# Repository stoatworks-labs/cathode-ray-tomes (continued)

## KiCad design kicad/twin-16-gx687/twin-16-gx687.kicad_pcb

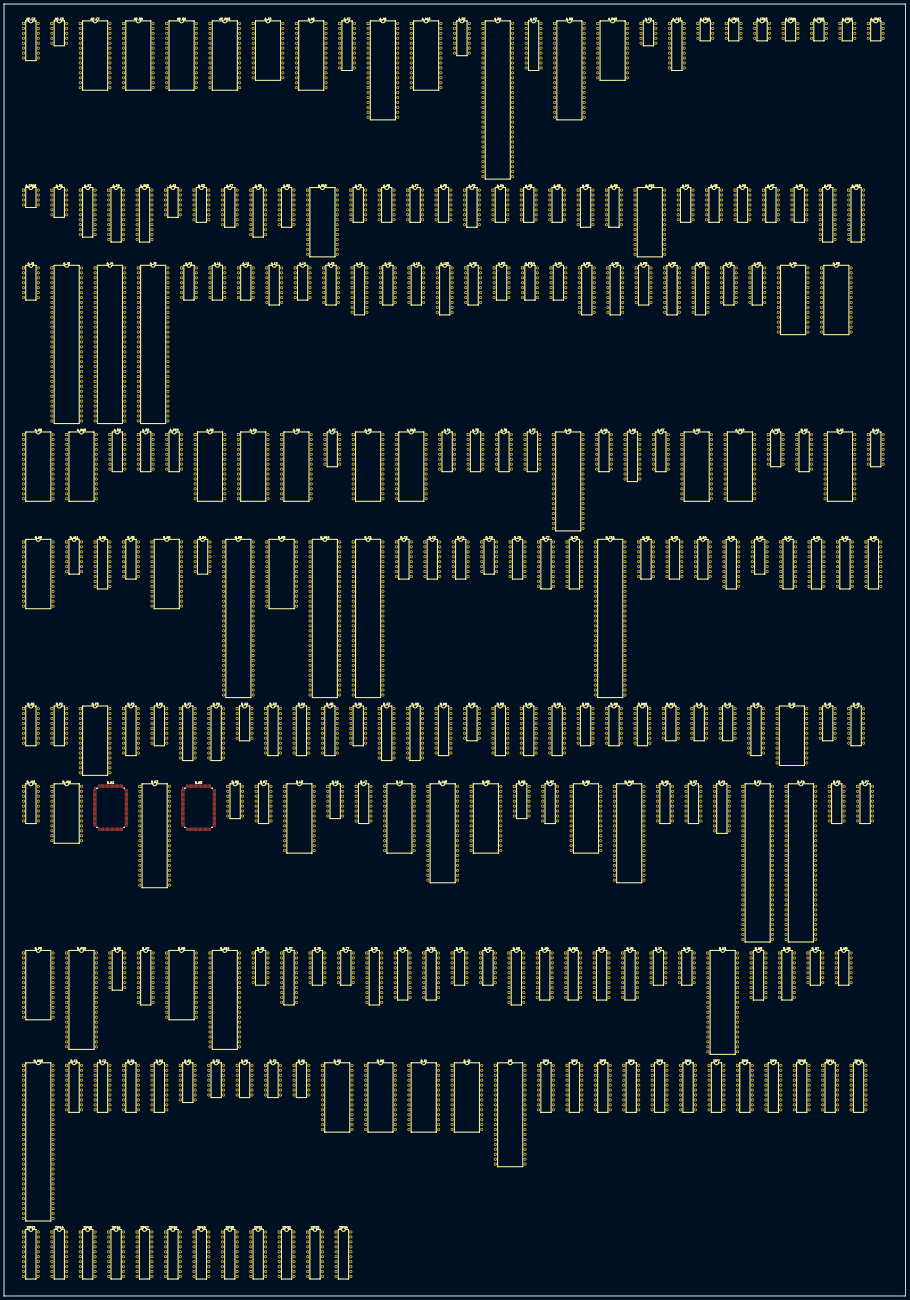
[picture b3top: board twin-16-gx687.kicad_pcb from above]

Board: 2 copper layers, 463.8 x 664.7 mm, 252 parts (0 on the bottom side), 1202 nets, no tracks yet.

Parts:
AP_C2: YM3012; DIP-16_W7.62mm
AP_C5: 007340; DIP-10_W7.62mm
AP_C7: 23C1000; DIP-28_W15.24mm
AP_R4, AP_R6, AP_R10: 27C512; DIP-28_W15.24mm
A_A3: YM2151; DIP-24_W15.24mm
A_A5: 23C1000; DIP-28_W15.24mm
A_A7: 74LS273; DIP-20_W7.62mm
A_A8: Z80CPU; DIP-40_W15.24mm
A_A10: 27C256; DIP-28_W15.24mm
A_B2: uPC324; DIP-14_W7.62mm
A_B4: 007232; DIP-64_W15.24mm
A_B7: 74LS273; DIP-20_W7.62mm
A_B8: μPD7759; DIP-40_W15.24mm
A_B10: 2128SL; DIP-24_W15.24mm
A_C4: 007340; DIP-10_W7.62mm
A_C10: 74LS374; DIP-20_W7.62mm
A_CRA1, A_CRA2, A_CRA3, A_CRA4, A_CRA5, A_CRA6, A_CRA7, A_CRA8: 005273; DIP-8_W7.62mm
A_D1: MB3722; DIP-12_W7.62mm
A_D7: 74LS273; DIP-20_W7.62mm
A_D9, A_D10: 007644; DIP-22_W7.62mm
A_E1: 005924; DIP-12_W7.62mm
A_E3: uPC324; DIP-14_W7.62mm
A_E7: 74LS138; DIP-16_W7.62mm
A_E8: PAL16L8’; DIP-20_W7.62mm
A_E9: 74LS157; DIP-16_W7.62mm
A_E10: 6264SL; DIP-28_W15.24mm
A_F3: uPC324; DIP-14_W7.62mm
A_F6, A_F8: 74LS74; DIP-14_W7.62mm
A_F7: 74LS04; DIP-14_W7.62mm
A_F9: 74LS157; DIP-16_W7.62mm
A_G4: uPC324; DIP-14_W7.62mm
A_G5: 74LS74; DIP-14_W7.62mm
A_G6: 74LS00; DIP-14_W7.62mm
A_G8, A_G9: 74LS157; DIP-16_W7.62mm
A_G10: 6264SL; DIP-28_W15.24mm
A_H4: 74LS08; DIP-14_W7.62mm
A_H5, A_H6: 74LS74; DIP-14_W7.62mm
A_H7: 74LS04; DIP-14_W7.62mm
A_H8: 74LS07; DIP-14_W7.62mm
A_H9, A_H10: 007644; DIP-22_W7.62mm
A_J1: 74LS32; DIP-14_W7.62mm
A_J2: 007791; DIP-64_W15.24mm
A_J4, A_J8: 68000; DIP-64_W15.24mm
A_K1: 74LS32; DIP-14_W7.62mm
A_L1: 74LS07; DIP-14_W7.62mm
A_L2: 74LS00; DIP-14_W7.62mm
A_L3: 74LS138; DIP-16_W7.62mm
A_L4: 74LS74; DIP-14_W7.62mm
A_L5, A_L9: 74LS367; DIP-16_W7.62mm
A_L6, A_L10: 74LS244; DIP-20_W7.62mm
A_L8: 74HC367; DIP-16_W7.62mm
A_M2: 74LS253; DIP-16_W7.62mm
A_M3: 74LS74; DIP-14_W7.62mm
A_M3.4: 74LS02; DIP-14_W7.62mm
A_M4: 74LS21; DIP-14_W7.62mm
A_M5, A_M6, A_M9, A_M10: 74LS245; DIP-20_W7.62mm
A_M8: 74LS138; DIP-16_W7.62mm
A_N2: 74LS253; DIP-16_W7.62mm
A_N3: 74LS139; DIP-16_W7.62mm
A_N4, A_N6, A_N8, A_N10: 27C512; DIP-28_W15.24mm
A_O2: 74LS253; DIP-16_W7.62mm
A_O3: 74LS257; DIP-16_W7.62mm
A_PP2: 74LS253; DIP-16_W7.62mm
A_R8: 27C512; DIP-28_W15.24mm
A_S4, A_S6: 6264SL; DIP-28_W15.24mm
A_S7: 74LS30; DIP-14_W7.62mm
A_S8, A_S10: 27C512; DIP-28_W15.24mm
A_T4: 74LS257; DIP-16_W7.62mm
A_T5, A_T7: 74LS138; DIP-16_W7.62mm
A_T6: 74LS157; DIP-16_W7.62mm
A_U1: 007327; DIP-40_W15.24mm
A_U4: 74LS367; DIP-16_W7.62mm
A_U6: 74LS273; DIP-20_W7.62mm
A_U7: 74LS174; DIP-16_W7.62mm
A_U8, A_U10: 6264SL; DIP-28_W15.24mm
A_V10: 74LS74; DIP-14_W7.62mm
B_A2: 74LS157; DIP-16_W7.62mm
B_A3: 6264SL; DIP-28_W15.24mm
B_A4: 74LS27; DIP-14_W7.62mm
B_A8: SRAM8K8B; DIP-28_W15.24mm
B_A11: 74LS32; DIP-14_W7.62mm
B_B1: 74LS244; DIP-20_W7.62mm
B_B2: 74LS157; DIP-16_W7.62mm
B_B3: 6264SL; DIP-28_W15.24mm
B_B4: 74LS27; DIP-14_W7.62mm
B_B6: 007779; DIP-64_W15.24mm
B_B8: SRAM8K8B; DIP-28_W15.24mm
B_B10: 007780; DIP-64_W15.24mm
B_C1: 007782; DIP-64_W15.24mm
B_C2: 74LS157; DIP-16_W7.62mm
B_C3, B_C4: 74LS174; DIP-16_W7.62mm
B_C5: 74LS32; DIP-14_W7.62mm
B_C6: 74LS138; DIP-16_W7.62mm
B_C7, B_C8: 74LS245; DIP-20_W7.62mm
B_C11: 007781; DIP-64_W15.24mm
B_D2: 74LS157; DIP-16_W7.62mm
B_D3, B_D4: 74LS174; DIP-16_W7.62mm
B_D5, B_D7, B_D8: 74LS245; DIP-20_W7.62mm
B_D6: 74LS02; DIP-14_W7.62mm
B_E2: 74LS273; DIP-20_W7.62mm
B_E5: 74LS245; DIP-20_W7.62mm
B_E6: 74LS153; DIP-16_W7.62mm
B_F2: 74LS157; DIP-16_W7.62mm
B_F3: 27C128; DIP-28_W15.24mm
B_F5: 74LS245; DIP-20_W7.62mm
B_F6: 74LS174; DIP-16_W7.62mm
B_F7, B_F8: 007644; DIP-22_W7.62mm
B_G2: 74LS04; DIP-14_W7.62mm
B_G3, B_G4: 74LS273; DIP-20_W7.62mm
B_G5: 74LS245; DIP-20_W7.62mm
B_G6: 74LS174; DIP-16_W7.62mm
B_G7, B_G8: 007644; DIP-22_W7.62mm
B_H1: 74LS244; DIP-20_W7.62mm
B_H2: 74LS86; DIP-14_W7.62mm
B_H3, B_H4: 74LS273; DIP-20_W7.62mm
B_H5: 74LS245; DIP-20_W7.62mm
B_H8, B_H9, B_H10: 74LS153; DIP-16_W7.62mm
B_H11: 74LS74; DIP-14_W7.62mm
B_J1, B_J2: 74LS86; DIP-14_W7.62mm
B_J5: 74LS245; DIP-20_W7.62mm
B_J6, B_J11: GAL22V10; DIP-24_W15.24mm
B_J8: 74LS32; DIP-14_W7.62mm
B_J9, B_J10: 74LS153; DIP-16_W7.62mm
B_K1: 007783; PQFP-100_14x20mm_P0.65mm
B_K3: 007784; DIP-42_W15.24mm
B_K5: 007785; PQFP-100_14x20mm_P0.65mm
B_K6: 74LS32; DIP-14_W7.62mm
B_K7: 74LS157; DIP-16_W7.62mm
B_L3: 6264SL; DIP-28_W15.24mm
B_L6: 74LS04; DIP-14_W7.62mm
B_L7: 74LS157; DIP-16_W7.62mm
B_L8: SRAM32K8B; DIP-28_W15.24mm
B_L10: 23C4100; DIP-40_W15.24mm
B_M3: 6264SL; DIP-28_W15.24mm
B_M6: 74LS00; DIP-14_W7.62mm
B_M7: 74LS157; DIP-16_W7.62mm
B_M8: SRAM32K8B; DIP-28_W15.24mm
B_M10: 23C4100; DIP-40_W15.24mm
B_N6, B_N7: 74LS157; DIP-16_W7.62mm
B_P1: PAL16L8’; DIP-20_W7.62mm
B_P2, B_P4: 007786; DIP-64_W15.24mm
B_P6, B_P7: 74LS157; DIP-16_W7.62mm
B_P8: SRAM32K8B; DIP-28_W15.24mm
B_P10: 23C4100; DIP-40_W15.24mm
B_R6: 74LS157; DIP-16_W7.62mm
B_R7: 007644; DIP-22_W7.62mm
B_R8: SRAM32K8B; DIP-28_W15.24mm
B_R10: 23C4100; DIP-40_W15.24mm
B_S6: 74LS20; DIP-14_W7.62mm
B_S7: 007644; DIP-22_W7.62mm
B_T6: 74LS32; DIP-14_W7.62mm
B_T7: 74LS02; DIP-14_W7.62mm
B_T8: 007644; DIP-22_W7.62mm
B_T9, B_T10: 74LS374; DIP-20_W7.62mm
B_U6: 74LS32; DIP-14_W7.62mm
B_U7: 74LS02; DIP-14_W7.62mm
B_U8: 007644; DIP-22_W7.62mm
B_U9, B_U10: 74LS374; DIP-20_W7.62mm
B_V5, B_V6: 74LS244; DIP-20_W7.62mm
B_V7, B_V8: 74LS32; DIP-14_W7.62mm
B_W1: 007787; DIP-42_W15.24mm
B_W5, B_W6: 74LS244; DIP-20_W7.62mm
B_W7, B_W8: 74LS32; DIP-14_W7.62mm
B_W10: 007786; DIP-64_W15.24mm
D_C1, D_C2: 74LS245; DIP-20_W7.62mm
D_D1, D_D2: 74LS245; DIP-20_W7.62mm
D_E1: 74LS174; DIP-16_W7.62mm
D_E2: 74LS32; DIP-14_W7.62mm
D_F1: 74LS04; DIP-14_W7.62mm
D_F2: 74LS32; DIP-14_W7.62mm
D_G1: 74LS32; DIP-14_W7.62mm
D_G2: 6264SL; DIP-28_W15.24mm
D_H2: 6264SL; DIP-28_W15.24mm
D_I2: 6264SL; DIP-28_W15.24mm
D_J2: 6264SL; DIP-28_W15.24mm
W3: 007787; DIP-42_W15.24mm
ZIP1, ZIP2, ZIP3, ZIP4, ZIP5, ZIP6, ZIP7, ZIP8, ZIP9, ZIP10, ZIP11, ZIP12, ZIP13, ZIP14, ZIP15, ZIP16, ZIP17, ZIP18, ZIP19, ZIP20, ZIP21, ZIP22, ZIP23, ZIP24: 4464Z; DIP-20_W7.62mm

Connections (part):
+12V: A_D1.10, A_E1.11, A_E3.4, A_F3.4
/1C0: B_C11.50, B_J8.10, B_J10.5
/1C1: B_C11.49, B_J8.9, B_J10.11
/1C2: B_C11.31, B_J8.13, B_J9.5
/1C3: B_C11.30, B_J8.12, B_J9.11
/1C4: B_C11.29, B_H10.5
/1C5: B_C11.2, B_H10.11
/1C6: B_C11.1, B_H8.5, B_J11.11
/1V: B_B6.1, B_C1.50, B_D3.3
/2C0: B_C11.57, B_J10.6, B_J11.4
/2C1: B_C11.56, B_J10.10, B_J11.17
/2C2: B_C11.55, B_J9.6, B_J11.18
/2C3: B_C11.54, B_J9.10, B_J11.19
/2C4: B_C11.53, B_H10.6
/2C5: B_C11.52, B_H10.10
/2C6: B_C11.51, B_H8.6, B_J11.13
/2V: B_C1.51, B_D3.4
/4V: B_C1.52, B_D3.6
/8H: B_C1.46, B_D2.6, B_P1.4
/8V: B_C1.53, B_C2.13
/16H: B_C1.45, B_D2.10
/16V: B_B2.3, B_C1.54
/32H: B_C1.44, B_D2.13
/32V: B_B2.6, B_C1.55
/64H: B_C1.43, B_C2.3
/64V: B_B2.10, B_C1.56
/128H: B_C1.42, B_C2.6
/128V: B_B2.13, B_C1.57
/256H: B_C1.41, B_C2.10
/AB1: AP_R4.10, AP_R6.10, A_E9.14, A_F7.3, A_L6.18, A_M2.14, A_N2.14, A_N4.10, A_N6.10, A_O2.14, A_O3.1, A_PP2.14, A_S4.10, A_S6.10, A_T4.1, A_U1.37, B_B6.25, B_C6.1, B_D2.5, B_K1.16, D_C2.2
/AB2: AP_R4.9, AP_R6.9, A_G9.2, A_L6.16, A_M2.2, A_N2.2, A_N4.9, A_N6.9, A_O2.2, A_PP2.2, A_S4.9, A_S6.9, A_U1.35, B_B6.24, B_C6.2, B_D2.11, B_K1.15, D_C2.3
/AB3: AP_R4.8, AP_R6.8, A_G9.5, A_L6.14, A_N4.8, A_N6.8, A_S4.8, A_S6.8, A_U1.34, B_B6.23, B_C6.3, B_D2.14, B_K1.14, D_C2.4
/AB4: AP_R4.7, AP_R6.7, A_G9.11, A_L6.12, A_N4.7, A_N6.7, A_S4.7, A_S6.7, A_U1.33, B_B6.22, B_C2.2, B_K1.13, D_C2.5
/AB5: AP_R4.6, AP_R6.6, A_G9.14, A_L6.9, A_N4.6, A_N6.6, A_S4.6, A_S6.6, A_U1.32, B_B6.21, B_C2.5, B_K1.12, D_C2.6
/AB6: AP_R4.5, AP_R6.5, A_G8.2, A_L6.7, A_N4.5, A_N6.5, A_S4.5, A_S6.5, A_U1.31, B_B6.20, B_C2.11, B_K1.11, D_C2.7
/AB7: AP_R4.4, AP_R6.4, A_G8.5, A_L6.5, A_N4.4, A_N6.4, A_S4.4, A_S6.4, A_U1.30, B_B6.19, B_C2.14, B_K1.10, D_C2.8
/AB8: AP_R4.3, AP_R6.3, A_G8.11, A_L6.3, A_N4.3, A_N6.3, A_S4.3, A_S6.3, A_U1.29, B_B2.2, B_B6.18, B_K1.9, D_C2.9
/AB9: AP_R4.25, AP_R6.25, A_G8.14, A_L5.3, A_N4.25, A_N6.25, A_S4.25, A_S6.25, A_T6.2, B_B2.5, B_B6.17, B_K1.8, D_D2.2
/AB10: AP_R4.24, AP_R6.24, A_F9.2, A_L5.5, A_N4.24, A_N6.24, A_S4.24, A_S6.24, A_T6.5, B_B2.11, B_B6.15, B_K1.7, D_D2.3
/AB11: AP_R4.21, AP_R6.21, A_F9.5, A_L5.7, A_N4.21, A_N6.21, A_S4.21, A_S6.21, A_T6.11, B_B2.14, B_B6.14, B_K1.6
/AB12: AP_R4.23, AP_R6.23, A_F9.11, A_L5.9, A_N4.23, A_N6.23, A_S4.23, A_S6.23, A_T6.14, B_A2.2, B_B6.13, B_K1.5
/AB13: AP_R4.2, AP_R6.2, A_F9.14, A_L5.11, A_N4.2, A_N6.2, A_S4.2, A_S6.2, B_A2.5, B_E6.12, B_K1.4
/Battery Powered RAM/AB'1: D_C2.18, D_G2.10, D_H2.10, D_I2.10, D_J2.10
/Battery Powered RAM/AB'2: D_C2.17, D_G2.9, D_H2.9, D_I2.9, D_J2.9
/Battery Powered RAM/AB'3: D_C2.16, D_G2.8, D_H2.8, D_I2.8, D_J2.8
/Battery Powered RAM/AB'4: D_C2.15, D_G2.7, D_H2.7, D_I2.7, D_J2.7
/Battery Powered RAM/AB'5: D_C2.14, D_G2.6, D_H2.6, D_I2.6, D_J2.6
/Battery Powered RAM/AB'6: D_C2.13, D_G2.5, D_H2.5, D_I2.5, D_J2.5
/Battery Powered RAM/AB'7: D_C2.12, D_G2.4, D_H2.4, D_I2.4, D_J2.4
/Battery Powered RAM/AB'8: D_C2.11, D_G2.3, D_H2.3, D_I2.3, D_J2.3
/Battery Powered RAM/AB'9: D_D2.18, D_G2.25, D_H2.25, D_I2.25, D_J2.25
/Battery Powered RAM/AB'10: D_D2.17, D_F1.3, D_G1.10
/Battery Powered RAM/DB'0: D_C1.18, D_G2.11, D_H2.11
/Battery Powered RAM/DB'1: D_C1.17, D_G2.12, D_H2.12
/Battery Powered RAM/DB'2: D_C1.16, D_G2.13, D_H2.13
/Battery Powered RAM/DB'3: D_C1.15, D_G2.15, D_H2.15
/Battery Powered RAM/DB'4: D_C1.14, D_G2.16, D_H2.16
/Battery Powered RAM/DB'5: D_C1.13, D_G2.17, D_H2.17
/Battery Powered RAM/DB'6: D_C1.12, D_G2.18, D_H2.18
/Battery Powered RAM/DB'7: D_C1.11, D_G2.19, D_H2.19
/Battery Powered RAM/DB'8: D_D1.18, D_E1.3, D_I2.11, D_J2.11
/Battery Powered RAM/DB'9: D_D1.17, D_E1.4, D_I2.12, D_J2.12
/Battery Powered RAM/DB'10: D_D1.16, D_E1.6, D_I2.13, D_J2.13
/Battery Powered RAM/DB'11: D_D1.15, D_E1.11, D_I2.15, D_J2.15
/Battery Powered RAM/DB'12: D_D1.14, D_E1.13, D_I2.16, D_J2.16
/Battery Powered RAM/DB'13: D_D1.13, D_I2.17, D_J2.17
/Battery Powered RAM/DB'14: D_D1.12, D_I2.18, D_J2.18
/Battery Powered RAM/DB'15: D_D1.11, D_I2.19, D_J2.19
/Battery Powered RAM/DB''8: D_E1.2, D_G2.24, D_H2.24, D_I2.24, D_J2.24
/Battery Powered RAM/DB''9: D_E1.5, D_G2.21, D_H2.21, D_I2.21, D_J2.21
/Battery Powered RAM/DB''10: D_E1.7, D_G2.23, D_H2.23, D_I2.23, D_J2.23
/Battery Powered RAM/DB''11: D_E1.10, D_G2.2, D_H2.2, D_I2.2, D_J2.2
/Battery Powered RAM/DB''12: D_E1.12, D_E2.2, D_F1.5
/Battery Powered RAM/MA16': D_D2.13, D_F1.1
/Battery Powered RAM/~CPURES': D_D2.11, D_E1.1
/Battery Powered RAM/~HRAMEN: D_F2.1, D_F2.5, D_F2.10, D_F2.11
/Battery Powered RAM/~IOCS': D_D2.12, D_G1.4
/Battery Powered RAM/~LRAMEN: D_E2.3, D_E2.4, D_E2.10, D_E2.13
/Battery Powered RAM/~MLWR': D_D2.15, D_E2.12, D_F2.9
/Battery Powered RAM/~MREAD2': D_C1.1, D_D1.1, D_D2.16, D_E2.5, D_F2.2
/Battery Powered RAM/~MUWR': D_D2.14, D_E2.9, D_F2.4
/Battery Powered RAM/~RAMEN: D_G2.20, D_H2.20, D_I2.20, D_J2.20
/Battery Powered RAM/~RAM: D_C1.19, D_D1.19, D_G1.2, D_G1.6, D_G1.9
/Battery Powered RAM/~RWEN: D_E2.1, D_F2.12, D_G1.8
/CHAPAGE: A_G5.5, B_K7.14
/CLK2: A_U1.40, A_U6.11, A_U7.9, B_H1.12
/CLK21: B_G3.11, B_H1.9, B_H3.11, B_H4.11, B_K1.50, B_K3.42, B_K5.25, B_P1.8, B_P2.37, B_P4.37, B_W1.14, W3.14
/CLK22: B_B1.12, B_B6.5, B_B10.17, B_C11.46, B_W10.37
/CPUCLK: A_E8.16, A_G5.11, A_L8.6, B_C1.39
/Color mixer/1C: B_J8.6, B_J11.10
/Color mixer/C6: A_T6.12, A_U1.20
/Color mixer/C7: A_T6.9, A_U1.19
/Color mixer/C8: A_T6.7, A_U1.18
/Color mixer/C9: A_T6.4, A_U1.17
/Color mixer/CB0: A_U1.28, A_U7.12
/Color mixer/CB1: A_U1.27, A_U7.15
/Color mixer/CB2: A_U1.26, A_U6.2
/Color mixer/CB3: A_U1.25, A_U6.5
/Color mixer/CB4: A_U1.24, A_U6.6
/Color mixer/CB5: A_U1.23, A_U6.9
/Color mixer/CB6: A_U1.22, A_U6.12
/Color mixer/COLOR0: A_U7.13, B_J10.7
/Color mixer/COLOR1: A_U7.14, B_J10.9
/Color mixer/COLOR2: A_U6.3, B_J9.7
/Color mixer/COLOR3: A_U6.4, B_J9.9
/Color mixer/COLOR4: A_U6.7, B_H10.7
/Color mixer/COLOR5: A_U6.8, B_H10.9
/Color mixer/COLOR6: A_U6.13, B_H8.7
/Color mixer/COLOR7: A_U6.14, B_H8.9
/Color mixer/COLOR8: A_U6.17, B_H9.7
/Color mixer/COLOR9: A_U6.18, B_H9.9
/Color mixer/FX: B_A11.6, B_J11.1
/Color mixer/SELA: B_H8.14, B_H9.14, B_H10.14, B_J9.14, B_J10.14, B_J11.20
/Color mixer/SELB: B_H8.2, B_H9.2, B_H10.2, B_J9.2, B_J10.2, B_J11.21
/Color mixer/~CBLK': A_U1.39, A_U7.5
/Color mixer/~SHADOW: A_U7.6, B_J11.23
/DB0: AP_R4.11, A_C10.3, A_D10.13, A_M2.9, A_M5.18, A_N4.11, A_S4.11, A_T4.4, A_T5.3, A_U1.10, A_U4.9, B_B6.26, B_C1.36, B_D7.2, B_E5.9, B_F6.3, B_G4.3, B_G5.2, B_G6.3, B_K3.22, D_C1.2
/DB1: AP_R4.12, A_C10.4, A_D10.14, A_M2.7, A_M5.17, A_N4.12, A_S4.12, A_T4.7, A_U1.9, A_U4.7, B_B6.27, B_D7.3, B_E5.8, B_F6.4, B_G4.4, B_G5.3, B_G6.4, B_K3.23, D_C1.3
/DB2: AP_R4.13, A_C10.7, A_D10.15, A_M5.16, A_N2.9, A_N4.13, A_S4.13, A_T4.12, A_U1.8, A_U4.5, B_B6.28, B_D7.4, B_E5.7, B_F6.6, B_G4.7, B_G5.4, B_G6.6, B_K3.24, D_C1.4
/DB3: AP_R4.15, A_C10.8, A_D10.16, A_M5.15, A_N2.7, A_N4.15, A_S4.15, A_T4.9, A_T5.8, A_U1.7, A_U4.3, B_B6.29, B_D7.5, B_E5.6, B_G4.8, B_G5.5, B_K3.25, D_C1.5
/DB4: AP_R4.16, A_C10.13, A_D10.17, A_M5.14, A_N4.16, A_O2.9, A_O3.4, A_S4.16, A_U1.6, B_B6.30, B_D7.6, B_E5.5, B_G4.13, B_G5.6, B_K3.26, D_C1.6
/DB5: AP_R4.17, A_C10.14, A_D10.18, A_M5.13, A_N4.17, A_O2.7, A_O3.7, A_S4.17, A_U1.5, B_B6.31, B_D7.7, B_E5.4, B_G4.14, B_G5.7, B_K3.27, D_C1.7
/DB6: AP_R4.18, A_C10.17, A_D10.19, A_M5.12, A_N4.18, A_O3.12, A_PP2.7, A_S4.18, A_U1.4, B_B6.33, B_D7.8, B_E5.3, B_G4.17, B_G5.8, B_K3.28, D_C1.8
/DB7: AP_R4.19, A_C10.18, A_D10.20, A_M5.11, A_N4.19, A_O3.9, A_PP2.9, A_S4.19, A_U1.3, B_B6.34, B_D7.9, B_E5.2, B_G4.18, B_G5.9, B_K3.29, D_C1.9
/DB8: AP_R6.11, A_H9.13, A_M6.18, A_N6.11, A_S6.11, B_B6.35, B_C7.2, B_D5.9, B_J5.2, B_K3.30, D_D1.2
/DB9: AP_R6.12, A_H9.14, A_M6.17, A_N6.12, A_S6.12, B_C7.3, B_D5.8, B_J5.3, B_K3.31, D_D1.3
/DB10: AP_R6.13, A_H9.15, A_M6.16, A_N6.13, A_S6.13, B_C7.4, B_D5.7, B_J5.4, B_K3.33, D_D1.4
/DB11: AP_R6.15, A_H9.16, A_M6.15, A_N6.15, A_S6.15, B_C7.5, B_D5.6, B_J5.5, B_K3.34, D_D1.5
/DB12: AP_R6.16, A_H9.17, A_M6.14, A_N6.16, A_S6.16, B_C7.6, B_D5.5, B_J5.6, B_K3.35, D_D1.6
/DB13: AP_R6.17, A_H9.18, A_M6.13, A_N6.17, A_S6.17, B_C7.7, B_D5.4, B_J5.7, B_K3.36, D_D1.7
/DB14: AP_R6.18, A_H9.19, A_M6.12, A_N6.18, A_S6.18, B_C7.8, B_D5.3, B_J5.8, B_K3.37, D_D1.8
/DB15: AP_R6.19, A_H9.20, A_M6.11, A_N6.19, A_S6.19, B_C7.9, B_D5.2, B_J5.9, B_K3.38, D_D1.9
/DMA: B_C1.4, B_K1.36, B_K3.3, B_P1.2
/DMAINIT: A_M3.4.2, A_M3.4.12, B_C1.6, B_J8.2, B_K5.77, B_K6.1, B_P1.11
/DMAON: A_T5.16, B_H11.2, B_K1.2
/FBREF: B_B1.3, B_K1.53, B_K5.76
/FX0: B_A11.10, B_H4.2, B_J10.3
/FX1: B_A11.9, B_H4.5, B_J10.13
/FX2: B_A11.12, B_H4.6, B_J9.3
/FX3: B_A11.13, B_H4.9, B_J9.13
/FX4: B_H4.12, B_H10.3
/FX5: B_H4.15, B_H10.13
/FX6: B_H4.16, B_H8.3
/FX7: B_H4.19, B_H8.13
/Fixed Layer/A0: B_A3.10, B_B3.10, B_D2.7
/Fixed Layer/A1: B_A3.9, B_B3.9, B_D2.9
/Fixed Layer/A2: B_A3.8, B_B3.8, B_D2.12
/Fixed Layer/A3: B_A3.7, B_B3.7, B_C2.4
/Fixed Layer/A4: B_A3.6, B_B3.6, B_C2.7
/Fixed Layer/A5: B_A3.5, B_B3.5, B_C2.9
/Fixed Layer/A6: B_A3.4, B_B3.4, B_C2.12
/Fixed Layer/A7: B_A3.3, B_B2.4, B_B3.3
/Fixed Layer/A8: B_A3.25, B_B2.7, B_B3.25
/Fixed Layer/A9: B_A3.24, B_B2.9, B_B3.24
/Fixed Layer/A10: B_A3.21, B_B2.12, B_B3.21
/Fixed Layer/A11: B_A2.4, B_A3.23, B_B3.23
/Fixed Layer/A12: B_A2.7, B_A3.2, B_B3.2
/Fixed Layer/D0: B_B3.11, B_D3.11, B_E5.11
/Fixed Layer/D1: B_B3.12, B_D3.13, B_E5.12
/Fixed Layer/D2: B_B3.13, B_D3.14, B_E5.13
/Fixed Layer/D3: B_B3.15, B_D4.3, B_E5.14
/Fixed Layer/D4: B_B3.16, B_D4.4, B_E5.15
/Fixed Layer/D5: B_B3.17, B_D4.6, B_E5.16
/Fixed Layer/D6: B_B3.18, B_D4.11, B_E5.17
/Fixed Layer/D7: B_B3.19, B_D4.13, B_E5.18
/Fixed Layer/D8: B_A3.11, B_D4.14, B_D5.11
/Fixed Layer/D9: B_A3.12, B_C4.3, B_D5.12
/Fixed Layer/D10: B_A3.13, B_C4.4, B_D5.13
/Fixed Layer/D11: B_A3.15, B_C4.6, B_D5.14
/Fixed Layer/D12: B_A3.16, B_C4.11, B_D5.15
/Fixed Layer/D13: B_A3.17, B_C4.13, B_D5.16
/Fixed Layer/D14: B_A3.18, B_C4.14, B_D5.17
/Fixed Layer/D15: B_A3.19, B_D5.18
/Fixed Layer/FX10: B_E2.12, B_F2.2
/Fixed Layer/FX11: B_E2.15, B_F2.5
/Fixed Layer/FX12: B_E2.16, B_F2.11
/Fixed Layer/FX13: B_E2.19, B_F2.14
/Fixed Layer/FX20: B_E2.2, B_F2.3
/Fixed Layer/FX21: B_E2.5, B_F2.6
/Fixed Layer/FX22: B_E2.6, B_F2.10
/Fixed Layer/FX23: B_E2.9, B_F2.13
/Fixed Layer/~OE: B_A3.22, B_B3.22, B_D2.4
/Fixed Layer/~P1HB: B_C3.9, B_E2.11, B_J1.8
/Fixed Layer/~P4H: B_C4.9, B_D3.9, B_D4.9, B_J1.3
/HFLIP: B_C1.30, B_C11.45, B_G4.5, B_J1.5, B_J1.13, B_J2.2, B_P1.5, B_P2.35, B_P4.35, B_W1.16, W3.16
/IO/COIN1: A_CRA2.8, A_T5.2
/IO/COIN2: A_CRA8.8, A_E1.6
/IO/Y3: A_CRA1.5, A_PP2.5
/IO/Y4: A_CRA1.7, A_PP2.6
/IO/Y5: A_CRA4.1, A_PP2.13
/IO/Y6: A_CRA4.3, A_PP2.12
/IO/Y7: A_CRA4.5, A_PP2.11
/IO/Y8: A_CRA4.7, A_PP2.10
/IO/Y9: A_CRA5.1, A_O2.3
/IO/Y10: A_CRA5.3, A_O2.4
/IO/Y11: A_CRA5.5, A_O2.5
/IO/Y12: A_CRA5.7, A_O2.6
/IO/Y13: A_CRA6.1, A_O2.13
/IO/Y14: A_CRA6.3, A_O2.12
/IO/Y15: A_CRA6.5, A_O2.11
/IO/Y16: A_CRA6.7, A_O2.10
/IO/Y17: A_CRA7.1, A_N2.3
/IO/Y18: A_CRA7.3, A_N2.4
/IO/Y19: A_CRA7.5, A_N2.5
/IO/Y20: A_CRA7.7, A_N2.6
/IO/Y21: A_CRA3.1, A_N2.13
/IO/Y22: A_CRA3.3, A_N2.12
/IO/Y23: A_CRA3.5, A_N2.11
/IO/Y24: A_CRA3.7, A_N2.10
/IO/Y25: A_CRA8.1, A_M2.3
/IO/Y26: A_CRA8.3, A_M2.4
/IO/Y27: A_CRA8.5, A_M2.5
/IO/Y28: A_CRA8.7, A_M2.6
/IO/Y29: A_CRA2.1, A_M2.13
/IO/Y30: A_CRA2.3, A_M2.12
/IO/Y31: A_CRA2.5, A_M2.11
/IO/Y32: A_CRA2.7, A_M2.10
/IO/~AFR: A_E1.2, A_T5.13
/IO/~SHOOT: A_M2.1, A_M2.15, A_N2.1, A_N2.15, A_O2.1, A_O2.15, A_PP2.1, A_PP2.15
/IO/~SOUND-DATA: A_C10.11, A_T5.14
/IO/~WDRES: A_E1.4, A_L8.2
/MA1: A_J2.4, A_J4.29, A_L6.2
/MA2: A_J2.3, A_J4.30, A_L6.4
/MA3: A_J2.2, A_J4.31, A_L6.6
/MA4: A_J4.32, A_L6.8
/MA5: A_J2.63, A_J4.33, A_L6.11
/MA6: A_J2.62, A_J4.34, A_L6.13
/MA7: A_J2.61, A_J4.35, A_L6.15
/MA8: A_J2.60, A_J4.36, A_L6.17
/MA9: A_J2.59, A_J4.37, A_L5.2
/MA10: A_J2.58, A_J4.38, A_L5.4
/MA11: A_J2.57, A_J4.39, A_L5.6
/MA12: A_J2.56, A_J4.40, A_L5.10
/MA13: A_J2.55, A_J4.41, A_L5.12
/MA14: A_J2.54, A_J4.42, A_L5.14
/MA15: AP_R4.27, AP_R6.27, A_J2.53, A_J4.43, A_N4.27, A_N6.27
/MA16: AP_R4.1, AP_R6.1, A_J2.52, A_J4.44, A_N4.1, A_N6.1, A_T5.4, D_D2.7
/MA17: A_J2.51, A_J4.45, A_L3.1, A_N3.2
/MA18: A_J2.50, A_J4.46, A_L3.2, A_N3.3
/MA19: A_J2.49, A_J4.47, A_L3.3
/MA20: A_J2.47, A_J4.48, A_K1.2, A_L2.5, A_L3.4
/MA21: A_J2.46, A_J4.50
/MA22: A_J2.45, A_J4.51
/MA23: A_G6.1, A_J2.44, A_J4.52
/Main CPU/AB14: AP_R4.26, AP_R6.26, A_L5.13, A_N4.26, A_N6.26
/Main CPU/BUSE: A_H7.1, A_J2.5
/Main CPU/CLK: A_J2.18, A_J4.15, A_L8.9
/Main CPU/MAS: A_G6.2, A_H7.12, A_L2.4
/Main CPU/MD0: A_J2.27, A_J4.5, A_M5.2
/Main CPU/MD1: A_J2.28, A_J4.4, A_M5.3
/Main CPU/MD2: A_J2.29, A_J4.3, A_M5.4
/Main CPU/MD3: A_J2.30, A_J4.2, A_M5.5
/Main CPU/MD4: A_J2.31, A_J4.1, A_M5.6
/Main CPU/MD5: A_J2.33, A_J4.64, A_M5.7
/Main CPU/MD6: A_J2.34, A_J4.63, A_M5.8
/Main CPU/MD7: A_J2.35, A_J4.62, A_M5.9
/Main CPU/MD8: A_J2.36, A_J4.61, A_M6.2
/Main CPU/MD9: A_J2.37, A_J4.60, A_M6.3
/Main CPU/MD10: A_J2.38, A_J4.59, A_M6.4
/Main CPU/MD11: A_J2.39, A_J4.58, A_M6.5
/Main CPU/MD12: A_J2.40, A_J4.57, A_M6.6
/Main CPU/MD13: A_J2.41, A_J4.56, A_M6.7
/Main CPU/MD14: A_J2.42, A_J4.55, A_M6.8
/Main CPU/MD15: A_J2.43, A_J4.54, A_M6.9
/Main CPU/~BERR: A_J2.1, A_J4.22
/Main CPU/~BGACK: A_J2.20, A_J4.12
/Main CPU/~BG: A_J2.21, A_J4.11
/Main CPU/~BR: A_J2.19, A_J4.13
/Main CPU/~DTACK: A_J2.22, A_J4.10, A_L1.2
/Main CPU/~HALT: A_J2.17, A_J4.17, A_L1.8
/Main CPU/~IPL0: A_J2.8, A_J4.25, A_L2.8
/Main CPU/~IPL1: A_H4.1, A_J2.9, A_J4.24, A_L2.9, A_M3.5
/Main CPU/~IPL2: A_H4.3, A_J2.10, A_J4.23
/Main CPU/~LDS: A_J2.24, A_J4.8, A_K1.12
/Main CPU/~MAS: A_H7.13, A_J2.26, A_J4.6, A_K1.1, A_L3.5
/Main CPU/~MWORKCS: A_L3.12, A_S4.20, A_S6.20
/Main CPU/~RESET: A_J2.15, A_J4.18, A_L1.10
/Main CPU/~UDS: A_J1.4, A_J2.25, A_J4.7
/N2H: B_K6.5, B_L6.8, B_R7.12, B_S7.12, B_T8.12, B_T9.11, B_T10.11, B_U8.12, B_U9.11, B_U10.11
/OBJBUFINIT: B_C1.5, B_H11.3, B_K1.55, B_K3.2, B_P1.7
/OCD0: B_J10.4, B_J11.6, W3.21
/OCD1: B_J10.12, B_J11.7, W3.20
/OCD2: B_J9.4, B_J11.8, W3.19
/OCD3: B_J9.12, B_J11.9, W3.18
/OCD4: B_H10.4, B_W1.21
/OCD5: B_H10.12, B_W1.20
/OCD6: B_H8.4, B_W1.19
/OCD7: B_H8.12, B_W1.18
/P1H: B_B1.6, B_C1.47, B_P1.3
/P1HB: B_B1.14, B_B6.4, B_B10.23, B_J1.10, B_J1.12, B_K5.46
/P2H: B_A2.1, B_B2.1, B_B4.2, B_B4.4, B_C1.17, B_C2.1, B_C5.2, B_D2.1, B_D6.3, B_D6.5, B_E6.14, B_J2.1, B_J2.4, B_J6.1, B_K7.1, B_L6.9, B_L7.1, B_M7.1, B_N6.1, B_N7.1, B_P7.3, B_P7.5
/P4H: B_C1.15, B_E6.2, B_J1.2, B_J1.4, B_J6.2
/P256VD: B_C1.23, B_D6.6, B_K5.53, B_M6.2, B_P2.33, B_P6.1, B_P7.1, B_R6.1, B_W1.17, B_W10.33, W3.17
/PI0: B_G4.6, B_J11.2
/PI1: B_G4.9, B_J11.3
/PI2: B_G4.12, B_J11.5
/R~W: A_H7.3, A_H7.11, A_J1.5, A_J2.23, A_J4.9, A_K1.13
/SA15: AP_R10.27, A_J8.43, A_N8.27, A_N10.27, A_R8.27, A_S8.27, A_S10.27, B_B10.55, B_L7.5
/SA16: AP_R10.1, A_J8.44, A_N8.1, A_N10.1, A_R8.1, A_S8.1, A_S10.1, B_B10.54, B_L7.11
/SA17: A_J8.45, A_M8.1, B_B10.53, B_L7.14
/SA18: A_J8.46, A_M8.2, B_K7.2
/SA19: A_J8.47, A_M8.3, A_T7.1, B_K7.5
/SA20: A_J8.48, A_T7.2, B_K7.11
/SA21: A_J8.50, A_T7.3
/SA22: A_J8.51, A_K1.5, A_M8.4, A_T7.6
/SA23: A_G6.4, A_J8.52, A_T7.4
/SAB1: AP_R10.10, A_E9.13, A_L10.18, A_N8.10, A_N10.10, A_R8.10, A_S8.10, A_S10.10, A_U8.2, A_U10.10, B_B6.36, B_B10.6, B_J6.9, B_K1.31
/SAB2: AP_R10.9, A_G9.3, A_L10.16, A_N8.9, A_N10.9, A_R8.9, A_S8.9, A_S10.9, A_U8.23, A_U10.9, B_B6.37, B_B10.5, B_K1.30, B_N7.2
/SAB3: AP_R10.8, A_G9.6, A_L10.14, A_N8.8, A_N10.8, A_R8.8, A_S8.8, A_S10.8, A_U8.21, A_U10.8, B_B6.38, B_B10.4, B_K1.29, B_N7.5
/SAB4: AP_R10.7, A_G9.10, A_L10.12, A_N8.7, A_N10.7, A_R8.7, A_S8.7, A_S10.7, A_U8.24, A_U10.7, B_B6.39, B_B10.3, B_K1.28, B_N7.11
/SAB5: AP_R10.6, A_G9.13, A_L10.9, A_N8.6, A_N10.6, A_R8.6, A_S8.6, A_S10.6, A_U8.25, A_U10.6, B_B6.40, B_B10.2, B_K1.27, B_N7.14
/SAB6: AP_R10.5, A_G8.3, A_L10.7, A_N8.5, A_N10.5, A_R8.5, A_S8.5, A_S10.5, A_U8.3, A_U10.5, B_B6.41, B_B10.1, B_K1.26, B_M7.2
/SAB7: AP_R10.4, A_G8.6, A_L10.5, A_N8.4, A_N10.4, A_R8.4, A_S8.4, A_S10.4, A_U8.4, A_U10.4, B_B6.42, B_B10.63, B_K1.25, B_M7.5
/SAB8: AP_R10.3, A_G8.10, A_L10.3, A_N8.3, A_N10.3, A_R8.3, A_S8.3, A_S10.3, A_U8.5, A_U10.3, B_B6.43, B_B10.62, B_K1.24, B_M7.11
/SAB9: AP_R10.25, A_G8.13, A_L9.3, A_N8.25, A_N10.25, A_R8.25, A_S8.25, A_S10.25, A_U8.6, A_U10.25, B_B6.44, B_B10.61, B_K1.23, B_M7.14
/SAB10: AP_R10.24, A_F9.3, A_L9.5, A_N8.24, A_N10.24, A_R8.24, A_S8.24, A_S10.24, A_U8.7, A_U10.24, B_B6.45, B_B10.60, B_K1.20, B_N6.2
/SAB11: AP_R10.21, A_F9.6, A_L9.7, A_N8.21, A_N10.21, A_R8.21, A_S8.21, A_S10.21, A_U8.8, A_U10.21, B_B6.59, B_B10.59, B_K1.19, B_N6.5
/SAB12: AP_R10.23, A_F9.10, A_L9.9, A_N8.23, A_N10.23, A_R8.23, A_S8.23, A_S10.23, A_U8.9, A_U10.23, B_B6.60, B_B10.58, B_K1.18, B_N6.11
/SAB13: AP_R10.2, A_F9.13, A_L9.11, A_N8.2, A_N10.2, A_R8.2, A_S8.2, A_S10.2, A_U8.10, A_U10.2, B_B10.57, B_E6.13, B_K1.17, B_N6.14
/SAB14: AP_R10.26, A_L9.13, A_N8.26, A_N10.26, A_R8.26, A_S8.26, A_S10.26, B_B10.56, B_L7.2
/SCPUCLK: A_J8.15, A_L8.5
/SDB0: A_D9.13, A_H6.12, A_M9.18, A_N8.11, A_R8.11, A_S8.11, A_U8.11, B_D8.2, B_F5.2, B_F8.13, B_G8.13, B_T8.13, B_U8.13
/SDB1: A_D9.14, A_F6.2, A_M9.17, A_N8.12, A_R8.12, A_S8.12, A_U8.12, B_D8.3, B_F5.3, B_F8.14, B_G8.14, B_T8.14, B_U8.14
/SDB2: A_D9.15, A_G5.2, A_M9.16, A_N8.13, A_R8.13, A_S8.13, A_U8.13, B_D8.4, B_F5.4, B_F8.15, B_G8.15, B_T8.15, B_U8.15
/SDB3: A_D9.16, A_M9.15, A_N8.15, A_R8.15, A_S8.15, A_U8.15, B_D8.5, B_F5.5, B_F8.16, B_G8.16, B_T8.16, B_U8.16
/SDB4: A_D9.17, A_M9.14, A_N8.16, A_R8.16, A_S8.16, A_U8.16, B_D8.6, B_F5.6, B_F8.17, B_G8.17, B_T8.17, B_U8.17
/SDB5: A_D9.18, A_M9.13, A_N8.17, A_R8.17, A_S8.17, A_U8.17, B_D8.7, B_F5.7, B_F8.18, B_G8.18, B_T8.18, B_U8.18
/SDB6: A_D9.19, A_M9.12, A_N8.18, A_R8.18, A_S8.18, A_U8.18, B_D8.8, B_F5.8, B_F8.19, B_G8.19, B_T8.19, B_U8.19
/SDB7: A_D9.20, A_M9.11, A_N8.19, A_R8.19, A_S8.19, A_U8.19, B_D8.9, B_F5.9, B_F8.20, B_G8.20, B_T8.20, B_U8.20
/SDB8: AP_R10.11, A_H10.13, A_M10.18, A_N10.11, A_S10.11, A_U10.11, B_C8.2, B_F7.13, B_G7.13, B_H5.2, B_R7.13, B_S7.13
/SDB9: AP_R10.12, A_H10.14, A_M10.17, A_N10.12, A_S10.12, A_U10.12, B_C8.3, B_F7.14, B_G7.14, B_H5.3, B_R7.14, B_S7.14
/SDB10: AP_R10.13, A_H10.15, A_M10.16, A_N10.13, A_S10.13, A_U10.13, B_C8.4, B_F7.15, B_G7.15, B_H5.4, B_R7.15, B_S7.15
/SDB11: AP_R10.15, A_H10.16, A_M10.15, A_N10.15, A_S10.15, A_U10.15, B_C8.5, B_F7.16, B_G7.16, B_H5.5, B_R7.16, B_S7.16
/SDB12: AP_R10.16, A_H10.17, A_M10.14, A_N10.16, A_S10.16, A_U10.16, B_C8.6, B_F7.17, B_G7.17, B_H5.6, B_R7.17, B_S7.17
/SDB13: AP_R10.17, A_H10.18, A_M10.13, A_N10.17, A_S10.17, A_U10.17, B_C8.7, B_F7.18, B_G7.18, B_H5.7, B_R7.18, B_S7.18
/SDB14: AP_R10.18, A_H10.19, A_M10.12, A_N10.18, A_S10.18, A_U10.18, B_C8.8, B_F7.19, B_G7.19, B_H5.8, B_R7.19, B_S7.19
/SDB15: AP_R10.19, A_H10.20, A_M10.11, A_N10.19, A_S10.19, A_U10.19, B_C8.9, B_F7.20, B_G7.20, B_H5.9, B_R7.20, B_S7.20
/Shared Resources/A0: A_E9.12, A_E10.10, A_G10.10
/Shared Resources/A1: A_E10.9, A_G9.4, A_G10.9
/Shared Resources/A2: A_E10.8, A_G9.7, A_G10.8
/Shared Resources/A3: A_E10.7, A_G9.9, A_G10.7
/Shared Resources/A4: A_E10.6, A_G9.12, A_G10.6
/Shared Resources/A5: A_E10.5, A_G8.4, A_G10.5
/Shared Resources/A6: A_E10.4, A_G8.7, A_G10.4
/Shared Resources/A7: A_E10.3, A_G8.9, A_G10.3
/Shared Resources/A8: A_E10.25, A_G8.12, A_G10.25
/Shared Resources/A9: A_E10.24, A_F9.4, A_G10.24
/Shared Resources/A10: A_E10.21, A_F9.7, A_G10.21
/Shared Resources/A11: A_E10.23, A_F9.9, A_G10.23
/Shared Resources/A12: A_E10.2, A_F9.12, A_G10.2
/Shared Resources/ID0: A_D9.10, A_D10.10, A_E10.11
/Shared Resources/ID1: A_D9.9, A_D10.9, A_E10.12
/Shared Resources/ID2: A_D9.8, A_D10.8, A_E10.13
/Shared Resources/ID3: A_D9.7, A_D10.7, A_E10.15
/Shared Resources/ID4: A_D9.6, A_D10.6, A_E10.16
/Shared Resources/ID5: A_D9.5, A_D10.5, A_E10.17
/Shared Resources/ID6: A_D9.4, A_D10.4, A_E10.18
/Shared Resources/ID7: A_D9.3, A_D10.3, A_E10.19
/Shared Resources/ID8: A_G10.11, A_H9.10, A_H10.10
/Shared Resources/ID9: A_G10.12, A_H9.9, A_H10.9
/Shared Resources/ID10: A_G10.13, A_H9.8, A_H10.8
/Shared Resources/ID11: A_G10.15, A_H9.7, A_H10.7
/Shared Resources/ID12: A_G10.16, A_H9.6, A_H10.6
/Shared Resources/ID13: A_G10.17, A_H9.5, A_H10.5
/Shared Resources/ID14: A_G10.18, A_H9.4, A_H10.4
/Shared Resources/ID15: A_G10.19, A_H9.3, A_H10.3
/Shared Resources/SNMMPX: A_D10.12, A_E8.5, A_E9.1, A_F9.1, A_G5.9, A_G8.1, A_G9.1, A_H9.12
/Shared Resources/~CLWR: A_E8.18, A_E10.27
/Shared Resources/~CUWR: A_E8.19, A_G10.27
/Shared Resources/~MCOMRD: A_D10.21, A_E8.12, A_H9.21
/Shared Resources/~MWREN: A_D10.2, A_E8.15, A_H9.2
/Shared Resources/~SCOMRD: A_D9.21, A_E8.13, A_H10.21
/Shared Resources/~SNMMPX: A_D9.12, A_E8.3, A_G5.8, A_G5.12, A_H10.12
/Shared Resources/~SWREN: A_D9.2, A_E8.14, A_H10.2
/Slave CPU/A1: A_J8.29, A_L10.2
/Slave CPU/A2: A_J8.30, A_L10.4
/Slave CPU/A3: A_J8.31, A_L10.6
/Slave CPU/A4: A_J8.32, A_L10.8
/Slave CPU/A5: A_J8.33, A_L10.11
/Slave CPU/A6: A_J8.34, A_L10.13
/Slave CPU/A7: A_J8.35, A_L10.15
/Slave CPU/A8: A_J8.36, A_L10.17
/Slave CPU/A9: A_J8.37, A_L9.2
/Slave CPU/A10: A_J8.38, A_L9.4
/Slave CPU/A11: A_J8.39, A_L9.6
/Slave CPU/A12: A_J8.40, A_L9.10
/Slave CPU/A13: A_J8.41, A_L9.12
/Slave CPU/A14: A_J8.42, A_L9.14
/Slave CPU/D0: A_J8.5, A_M9.2
/Slave CPU/D1: A_J8.4, A_M9.3
/Slave CPU/D2: A_J8.3, A_M9.4
/Slave CPU/D3: A_J8.2, A_M9.5
/Slave CPU/D4: A_J8.1, A_M9.6
/Slave CPU/D5: A_J8.64, A_M9.7
/Slave CPU/D6: A_J8.63, A_M9.8
/Slave CPU/D7: A_J8.62, A_M9.9
/Slave CPU/D8: A_J8.61, A_M10.2
/Slave CPU/D9: A_J8.60, A_M10.3
/Slave CPU/D10: A_J8.59, A_M10.4
/Slave CPU/D11: A_J8.58, A_M10.5
/Slave CPU/D12: A_J8.57, A_M10.6
/Slave CPU/D13: A_J8.56, A_M10.7
/Slave CPU/D14: A_J8.55, A_M10.8
/Slave CPU/D15: A_J8.54, A_M10.9
/Slave CPU/SINT16EN: A_F6.5, A_H5.4
/Slave CPU/~SAS: A_F7.1, A_J8.6, A_K1.4, A_M8.5, A_T7.5
/Slave CPU/~SODTACK: A_S7.6, A_V10.9
/Slave CPU/~SSYSFLAG: A_F6.3, A_G5.3, A_H6.11, A_M8.10
/Slave CPU/~SWORKCS: A_M8.12, A_U8.20, A_U10.20
/Slave CPU/~VRAMDTACK: A_S7.12, A_V10.5
/Sound/A0: A_A3.4, A_A8.30, A_A10.10, A_B10.8, A_F7.11
/Sound/A1: A_A8.31, A_A10.9, A_B4.59, A_B10.7
/Sound/A2: A_A8.32, A_A10.8, A_B4.60, A_B10.6
/Sound/A3: A_A8.33, A_A10.7, A_B4.61, A_B10.5
/Sound/A4: A_A8.34, A_A10.6, A_B10.4
/Sound/A5: A_A8.35, A_A10.5, A_B10.3
/Sound/A6: A_A8.36, A_A10.4, A_B10.2
/Sound/A7: A_A8.37, A_A10.3, A_B10.1
/Sound/A8: A_A8.38, A_A10.25, A_B10.23
/Sound/A9: A_A8.39, A_A10.24, A_B10.22
/Sound/A10: A_A8.40, A_A10.21, A_B10.19
/Sound/A11: A_A8.1, A_A10.23
/Sound/A12: A_A8.2, A_A10.2, A_E7.1
/Sound/A13: A_A8.3, A_A10.26, A_E7.2
/Sound/A14: A_A8.4, A_A10.27, A_E7.3
/Sound/A15: A_A8.5, A_A10.20, A_E7.6
/Sound/D0: A_A3.10, A_A8.14, A_A10.19, A_B4.1, A_B7.3, A_B10.17, A_C10.2, A_D7.3, A_F8.12, A_U4.13
/Sound/D1: A_A3.12, A_A8.15, A_A10.18, A_B4.2, A_B7.4, A_B10.16, A_C10.5, A_D7.4, A_F8.2
/Sound/D2: A_A3.13, A_A8.12, A_A10.17, A_B4.3, A_B7.7, A_B10.15, A_C10.6, A_D7.7
/Sound/D3: A_A3.14, A_A8.8, A_A10.16, A_B4.4, A_B7.8, A_B10.14, A_C10.9, A_D7.8
/Sound/D4: A_A3.15, A_A8.7, A_A10.15, A_B4.5, A_B7.13, A_B10.13, A_C10.12, A_D7.13
/Sound/D5: A_A3.16, A_A8.9, A_A10.13, A_B4.6, A_B7.14, A_B10.11, A_C10.15, A_D7.14
/Sound/D6: A_A3.17, A_A8.10, A_A10.12, A_B4.7, A_B7.17, A_B10.10, A_C10.16, A_D7.17
/Sound/D7: A_A3.18, A_A8.13, A_A10.11, A_B4.8, A_B7.18, A_B10.9, A_C10.19, A_D7.18
/Sound/REF2V5: A_E3.5, A_E3.12, A_F3.3, A_F3.10
/Sound/SMPA0: A_A5.10, A_B4.33
/Sound/SMPA1: A_A5.9, A_B4.34
/Sound/SMPA2: A_A5.8, A_B4.36
/Sound/SMPA3: A_A5.7, A_B4.38
/Sound/SMPA4: A_A5.6, A_B4.39
/Sound/SMPA5: A_A5.5, A_B4.41
/Sound/SMPA6: A_A5.4, A_B4.43
/Sound/SMPA7: A_A5.3, A_B4.45
/Sound/SMPA8: A_A5.25, A_B4.44
/Sound/SMPA9: A_A5.24, A_B4.42
/Sound/SMPA10: A_A5.21, A_B4.35
/Sound/SMPA11: A_A5.23, A_B4.40
/Sound/SMPA12: A_A5.2, A_B4.47
/Sound/SMPA13: A_A5.26, A_B4.46
/Sound/SMPA14: A_A5.27, A_B4.49
/Sound/SMPA15: A_A5.1, A_B4.50
/Sound/SMPA16: A_A5.22, A_B4.37
/Sound/SMPD0: A_A5.11, A_B4.25
/Sound/SMPD1: A_A5.12, A_B4.27
/Sound/SMPD2: A_A5.13, A_B4.29
/Sound/SMPD3: A_A5.15, A_B4.31
/Sound/SMPD4: A_A5.16, A_B4.30
/Sound/SMPD5: A_A5.17, A_B4.28
/Sound/SMPD6: A_A5.18, A_B4.26
/Sound/SMPD7: A_A5.19, A_B4.24
/Sound/UPDA0: AP_C7.10, A_B8.26
/Sound/UPDA1: AP_C7.9, A_B8.27
/Sound/UPDA2: AP_C7.8, A_B8.28
/Sound/UPDA3: AP_C7.7, A_B8.29
/Sound/UPDA4: AP_C7.6, A_B8.30
/Sound/UPDA5: AP_C7.5, A_B8.31
/Sound/UPDA6: AP_C7.4, A_B8.32
/Sound/UPDA7: AP_C7.3, A_B8.33
/Sound/UPDA8: AP_C7.25, A_B8.34
/Sound/UPDD0: AP_C7.11, A_A7.3, A_B8.35
/Sound/UPDD1: AP_C7.12, A_A7.4, A_B8.36
/Sound/UPDD2: AP_C7.13, A_A7.7, A_B8.37
/Sound/UPDD3: AP_C7.15, A_A7.8, A_B8.38
/Sound/UPDD4: AP_C7.16, A_A7.13, A_B8.39
/Sound/UPDD5: AP_C7.17, A_A7.14, A_B8.1
/Sound/UPDD6: AP_C7.18, A_A7.17, A_B8.2
/Sound/UPDD7: AP_C7.19, A_A7.18, A_B8.3
/Sound/~BSY: A_E7.7, A_U4.15
/Sound/~DACS: A_B4.62, A_E7.12
/Sound/~MREQ: A_A8.19, A_E7.5
/Sound/~RD: A_A3.6, A_A8.21, A_A10.22, A_B10.20
/Sound/~RESET: A_E7.14, A_F8.3
/Sound/~RFSH: A_A8.28, A_F7.13
/Sound/~VDIN: A_B7.11, A_E7.10
/Sound/~VST: A_E7.9, A_F8.11
/Sound/~WR: A_A3.5, A_A8.22, A_B10.21
/Sprite Frame Buffers/C0: B_K5.83, B_V5.2, B_V5.11, B_V6.2, B_V6.11
/Sprite Frame Buffers/C1: B_K5.82, B_V5.4, B_V5.13, B_V6.4, B_V6.13
/Sprite Frame Buffers/C2: B_K5.81, B_V5.6, B_V5.15, B_V6.6, B_V6.15
/Sprite Frame Buffers/C3: B_K5.80, B_V5.8, B_V5.17, B_V6.8, B_V6.17
/Sprite Frame Buffers/CX0: B_K5.2, B_W5.2, B_W5.11, B_W6.2, B_W6.11
/Sprite Frame Buffers/CX1: B_K5.3, B_W5.4, B_W5.13, B_W6.4, B_W6.13
/Sprite Frame Buffers/CX2: B_K5.4, B_W5.6, B_W5.15, B_W6.6, B_W6.15
/Sprite Frame Buffers/CX3: B_K5.5, B_W5.8, B_W5.17, B_W6.8, B_W6.17
/Sprite Frame Buffers/FA0: B_P2.15, ZIP21.20, ZIP23.20
/Sprite Frame Buffers/FA1: B_P2.14, ZIP21.19, ZIP23.19
/Sprite Frame Buffers/FA2: B_P2.13, ZIP21.18, ZIP23.18
/Sprite Frame Buffers/FA3: B_P2.12, ZIP21.17, ZIP23.17
/Sprite Frame Buffers/FA4: B_P2.11, ZIP21.14, ZIP23.14
/Sprite Frame Buffers/FA5: B_P2.10, ZIP21.13, ZIP23.13
/Sprite Frame Buffers/FA6: B_P2.9, ZIP21.12, ZIP23.12
/Sprite Frame Buffers/FA7: B_P2.8, ZIP21.16, ZIP23.16
/Sprite Frame Buffers/FA20: B_P4.15, ZIP13.20, ZIP15.20
/Sprite Frame Buffers/FA21: B_P4.14, ZIP13.19, ZIP15.19
/Sprite Frame Buffers/FA22: B_P4.13, ZIP13.18, ZIP15.18
/Sprite Frame Buffers/FA23: B_P4.12, ZIP13.17, ZIP15.17
/Sprite Frame Buffers/FA24: B_P4.11, ZIP13.14, ZIP15.14
/Sprite Frame Buffers/FA25: B_P4.10, ZIP13.13, ZIP15.13
/Sprite Frame Buffers/FA26: B_P4.9, ZIP13.12, ZIP15.12
/Sprite Frame Buffers/FA27: B_P4.8, ZIP13.16, ZIP15.16
/Sprite Frame Buffers/FB0: B_P2.25, ZIP22.20, ZIP24.20
/Sprite Frame Buffers/FB1: B_P2.24, ZIP22.19, ZIP24.19
/Sprite Frame Buffers/FB2: B_P2.23, ZIP22.18, ZIP24.18
/Sprite Frame Buffers/FB3: B_P2.22, ZIP22.17, ZIP24.17
/Sprite Frame Buffers/FB4: B_P2.21, ZIP22.14, ZIP24.14
/Sprite Frame Buffers/FB5: B_P2.20, ZIP22.13, ZIP24.13
/Sprite Frame Buffers/FB6: B_P2.19, ZIP22.12, ZIP24.12
/Sprite Frame Buffers/FB7: B_P2.18, ZIP22.16, ZIP24.16
/Sprite Frame Buffers/FB20: B_P4.25, ZIP14.20, ZIP16.20
/Sprite Frame Buffers/FB21: B_P4.24, ZIP14.19, ZIP16.19
/Sprite Frame Buffers/FB22: B_P4.23, ZIP14.18, ZIP16.18
/Sprite Frame Buffers/FB23: B_P4.22, ZIP14.17, ZIP16.17
/Sprite Frame Buffers/FB24: B_P4.21, ZIP14.14, ZIP16.14
/Sprite Frame Buffers/FB25: B_P4.20, ZIP14.13, ZIP16.13
/Sprite Frame Buffers/FB26: B_P4.19, ZIP14.12, ZIP16.12
/Sprite Frame Buffers/FB27: B_P4.18, ZIP14.16, ZIP16.16
/Sprite Frame Buffers/FC0: B_P2.50, ZIP17.20, ZIP19.20
/Sprite Frame Buffers/FC1: B_P2.51, ZIP17.19, ZIP19.19
/Sprite Frame Buffers/FC2: B_P2.52, ZIP17.18, ZIP19.18
/Sprite Frame Buffers/FC3: B_P2.53, ZIP17.17, ZIP19.17
/Sprite Frame Buffers/FC4: B_P2.54, ZIP17.14, ZIP19.14
/Sprite Frame Buffers/FC5: B_P2.55, ZIP17.13, ZIP19.13
/Sprite Frame Buffers/FC6: B_P2.56, ZIP17.12, ZIP19.12
/Sprite Frame Buffers/FC7: B_P2.57, ZIP17.16, ZIP19.16
/Sprite Frame Buffers/FC20: B_P4.50, ZIP9.20, ZIP11.20
/Sprite Frame Buffers/FC21: B_P4.51, ZIP9.19, ZIP11.19
/Sprite Frame Buffers/FC22: B_P4.52, ZIP9.18, ZIP11.18
/Sprite Frame Buffers/FC23: B_P4.53, ZIP9.17, ZIP11.17
/Sprite Frame Buffers/FC24: B_P4.54, ZIP9.14, ZIP11.14
/Sprite Frame Buffers/FC25: B_P4.55, ZIP9.13, ZIP11.13
/Sprite Frame Buffers/FC26: B_P4.56, ZIP9.12, ZIP11.12
/Sprite Frame Buffers/FC27: B_P4.57, ZIP9.16, ZIP11.16
/Sprite Frame Buffers/FD0: B_P2.40, ZIP18.20, ZIP20.20
/Sprite Frame Buffers/FD1: B_P2.41, ZIP18.19, ZIP20.19
/Sprite Frame Buffers/FD2: B_P2.42, ZIP18.18, ZIP20.18
/Sprite Frame Buffers/FD3: B_P2.43, ZIP18.17, ZIP20.17
/Sprite Frame Buffers/FD4: B_P2.44, ZIP18.14, ZIP20.14
/Sprite Frame Buffers/FD5: B_P2.45, ZIP18.13, ZIP20.13
/Sprite Frame Buffers/FD6: B_P2.46, ZIP18.12, ZIP20.12
/Sprite Frame Buffers/FD7: B_P2.47, ZIP18.16, ZIP20.16
/Sprite Frame Buffers/FD20: B_P4.40, ZIP10.20, ZIP12.20
/Sprite Frame Buffers/FD21: B_P4.41, ZIP10.19, ZIP12.19
/Sprite Frame Buffers/FD22: B_P4.42, ZIP10.18, ZIP12.18
/Sprite Frame Buffers/FD23: B_P4.43, ZIP10.17, ZIP12.17
/Sprite Frame Buffers/FD24: B_P4.44, ZIP10.14, ZIP12.14
/Sprite Frame Buffers/FD25: B_P4.45, ZIP10.13, ZIP12.13
/Sprite Frame Buffers/FD26: B_P4.46, ZIP10.12, ZIP12.12
/Sprite Frame Buffers/FD27: B_P4.47, ZIP10.16, ZIP12.16
/Sprite Frame Buffers/HD2: B_K5.28, B_P2.3, B_P4.3
/Sprite Frame Buffers/HD3: B_K5.29, B_P2.4, B_P4.4
/Sprite Frame Buffers/HD4: B_K5.30, B_P2.5, B_P4.5
/Sprite Frame Buffers/HD5: B_K5.31, B_P2.6, B_P4.6
/Sprite Frame Buffers/HD6: B_K5.32, B_P2.7, B_P4.7
/Sprite Frame Buffers/HD7: B_K5.33, B_P2.26, B_P4.26
/Sprite Frame Buffers/HD8: B_K5.34, B_P2.27, B_P4.27
/Sprite Frame Buffers/HJ0: B_K5.26, B_P2.1, B_P4.1, B_W10.2
/Sprite Frame Buffers/HJ1: B_K5.27, B_P2.2, B_P4.2, B_W10.1
/Sprite Frame Buffers/OCHF: B_J2.5, B_K5.47, B_W10.35
/Sprite Frame Buffers/R0: B_W8.9, B_W10.25, W3.39, ZIP18.1
/Sprite Frame Buffers/R1: B_W8.10, B_W10.24, W3.40, ZIP18.3
/Sprite Frame Buffers/R2: B_W8.12, B_W10.23, W3.41, ZIP18.6
/Sprite Frame Buffers/R3: B_W8.13, B_W10.22, W3.42, ZIP18.7
/Sprite Frame Buffers/R4: B_V6.18, B_W1.39, ZIP20.7
/Sprite Frame Buffers/R5: B_V6.16, B_W1.40, ZIP20.6
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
